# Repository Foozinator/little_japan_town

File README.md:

# Little Japan Town

Arduino and ESP8266 enhancements to miniature flat-pack Japanese shop models.

The models are small laser-cut wooden kits. This project adds lighting, sensing, and wireless control to bring them to life on a shelf or diorama layout.

## Projects

### choshi_no_shitamachi
PlatformIO project targeting an Arduino Nano (ATmega328). Starting point for shop lighting and sensor integration.

### cornerstone
KiCad schematic and PCB layout for a custom carrier board — consolidates power regulation and wiring for the shop electronics.

## Hardware

Key components in [`parts_bin.md`](parts_bin.md):

- **Arduino Nano × 5** — main microcontroller for most shops
- **NodeMCU Amica × 2, Heltec HTIT-W8266 × 1, ESP-01 × 1** — ESP8266-based WiFi nodes for wireless control or monitoring
- **AOSONG AM2302** — DHT22 temperature/humidity sensor
- **Dallas DS18B20 × 3** — 1-Wire temperature sensors; multiple units share one data line
- **RCWL-0516** — microwave Doppler motion sensor (detects through walls/facades)
- **Sharp GP2D120X** — IR proximity sensor, 4–30 cm range
- **OKI-78SR-3.3 × 2** — efficient 3.3 V switching regulators for the ESP8266 modules
- **MOC3043 / MOC3023** — optoisolated triac drivers for any mains-voltage lighting effects

## Tools

- [PlatformIO](https://platformio.org/) for Arduino firmware
- [KiCad](https://www.kicad.org/) for PCB design

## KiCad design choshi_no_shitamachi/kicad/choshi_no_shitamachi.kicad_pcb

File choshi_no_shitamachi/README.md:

## Choshi no Shitamachi
# Izakaya kit

Base Model: https://www.cutebee.net/products/cutebee-diy-miniature-house-choshi-no-shitamachi

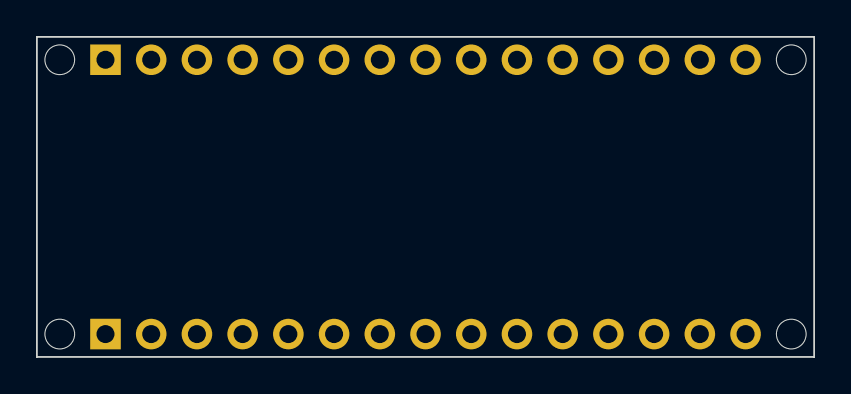
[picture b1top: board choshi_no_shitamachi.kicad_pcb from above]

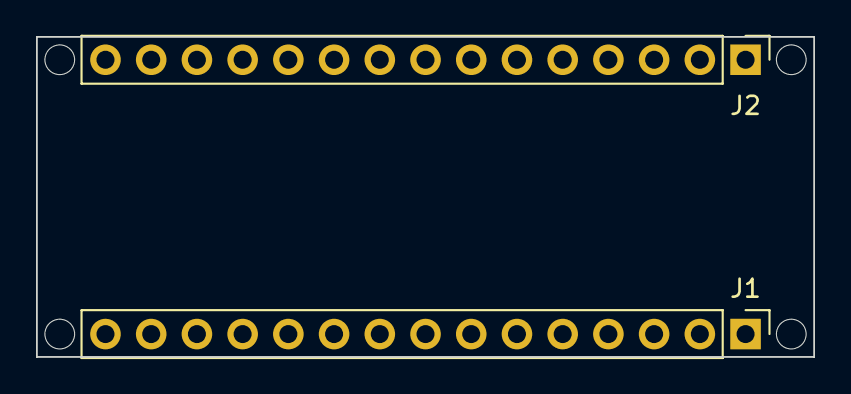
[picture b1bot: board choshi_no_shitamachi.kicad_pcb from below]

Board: 2 copper layers, 43.2 x 17.8 mm, 6 parts (2 on the bottom side), 2 nets, no tracks yet.

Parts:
J1: Analog; PinHeader_1x15_P2.54mm_Vertical
J2: Digital; PinHeader_1x15_P2.54mm_Vertical
MH1, MH2, MH3, MH4: MountingHole_65mil

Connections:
/~RESET: J1.13, J2.13
GND: J1.14, J2.12

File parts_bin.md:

| Component | Qty | Interface | Notes |
|---|---|---|---|
| Arduino Nano | x5 | USB/Digital/Analog | Unknown controller (CH340 vs FTDI matters for driver setup) |
| AOSONG AM2302 | x1 | Single-wire digital | DHT22 variant, pre-wired 3-pin connector, SN 17113CB16 (mfg week 13 2017), no breadboard wiring needed |
| Sharp GP2D120X | x1 | Analog | IR distance sensor, 4–30cm range, 3-pin JST connector, analog voltage output (nonlinear — needs lookup table or curve fitting) |
| NodeMCU Amica | x2 | WiFi (802.11b/g/n), Digital, Analog (1 pin) | ESP8266MOD, 3.3V logic, built-in USB-serial, 1x analog input (10-bit, 0–1V max — not 3.3V) |
| Heltec HTIT-W8266 | x1 | WiFi (802.11b/g/n), I2C (OLED), Digital, Analog | ESP8266EX, 3.3V logic, 0.91" 128x32 OLED (SSD1306), built-in LiPo charging circuit, same 1V A0 limit as NodeMCU |
| ESP-01 (ESP8266) | x1 | WiFi, 2x Digital GPIO | No USB — requires FTDI/CH340 adapter to program, GPIO0 must be grounded to enter flash mode, 3.3V only, limited I/O makes it best suited for dedicated single-purpose tasks |
| RCWL-0516 | x1 | Digital (single pin) | Microwave Doppler, 5–7m range, detects through non-metal obstacles, 4–28V input but 3.3V-compatible output, ~65mA active draw |
| Dallas DS18B20 | x3 | 1-Wire | -55–125°C range, ±0.5°C accuracy, unique 64-bit ID allows multiple sensors on a single wire, requires 4.7kΩ pull-up resistor, bare TO-92 |
| OKI-78SR-3.3 | x2 | Power | 3.3V/1.5A switching regulator, 7–36V input, ~82% efficiency, 7805-pinout compatible, no heatsink needed |
| Duemilanove | x1 | Digital, Analog, UART | ATmega328, fully Arduino-compatible, 5V logic |
| Netduino (rev.B) | x1 | Digital, Analog, UART (+ SD/Ethernet if Plus variant) | STM32, .NET Micro Framework — tooling largely dead, usable as generic STM32 board |
| Netduino Mini | x1 | Digital, UART, no USB | STM32F103, 3.3V, serial programming only, 24-pin DIP |
| MOC3043 | x1 | Digital (control side) | AC triac driver, zero-crossing detection built in, 6-DIP, isolates MCU from mains voltage — needs external triac (e.g. BTA16) for actual load switching |
| LM2596 module | x5 | Power | Adjustable DC-DC step-down, 4–40V in, 1.25–37V out, 3A max, adjust output via onboard trimmer — set and verify with multimeter before connecting anything |
| SRD-05VDC-SL-C module | x1 | Digital (active LOW typically) | 5V coil, 10A/250VAC contacts, onboard transistor driver, control signal from MCU pin — add flyback diode if using bare relay, module likely has one already |
| ACS711LC breakout (custom PCB) | x1 | Analog | Hall-effect current sensor, ±15.5A range, analog voltage output proportional to current, 3.3–5V supply, no isolation on the LC variant |
| MOC3023 | x4 | Digital (control side) | AC triac driver, no zero-crossing, 6-DIP, pairs with external triac for load switching — better for resistive loads than inductive |
| Futaba FP-S148 | x1 | 3-pin PWM input | Standard cheap servo |
| NeoPixel | x12
| AT24C256 | 5x | I2C | 256kBit EEPROM
| INA219 | 10x | I2C | Current sensing
| BH1750 | x1 | I2C | Ambient light sensing
| TTL to RS485 | 5x 

+ a handful of random resistors, LEDs, capacitors, ribbon cables, pins and sockets

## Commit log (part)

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2026-04-19 project creation
2026-04-19 documented standards and readme
2026-04-19 basic AM2302 and NeoPixel op
2026-04-19 added Claude and readme
2026-04-19 arranging standards
2026-05-03 * Started KiCad project * Shitamachi code now handles current and light sensors
2026-05-26 re-connection with RAM and Kubuntu
2026-06-03 new pieces purchased to parts bin
2026-06-07 Nearly full hardward check
2026-06-07 Full device set v1.0
2026-06-13 vibe-coded schematic test
2026-06-20 Adjusted NeoPixel symbols and footprints
2026-06-20 Footprint edit fixes
